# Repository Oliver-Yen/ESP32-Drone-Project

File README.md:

# ESP32-Drone-Project
This following project gets idea from a previous, broken DIY_drone_kit, and uses the ESP32-C6-Module as the MCU, while being controlled via WIFI or BT

TODO Add a distance, aclel., presu. , and an easy battery moniter    
TODO Add MOSFETs to drive the 4 coreless moters    
TODO Sch. drawing & PCB designing    
TODO Hardware code upload    
TODO HTML page design

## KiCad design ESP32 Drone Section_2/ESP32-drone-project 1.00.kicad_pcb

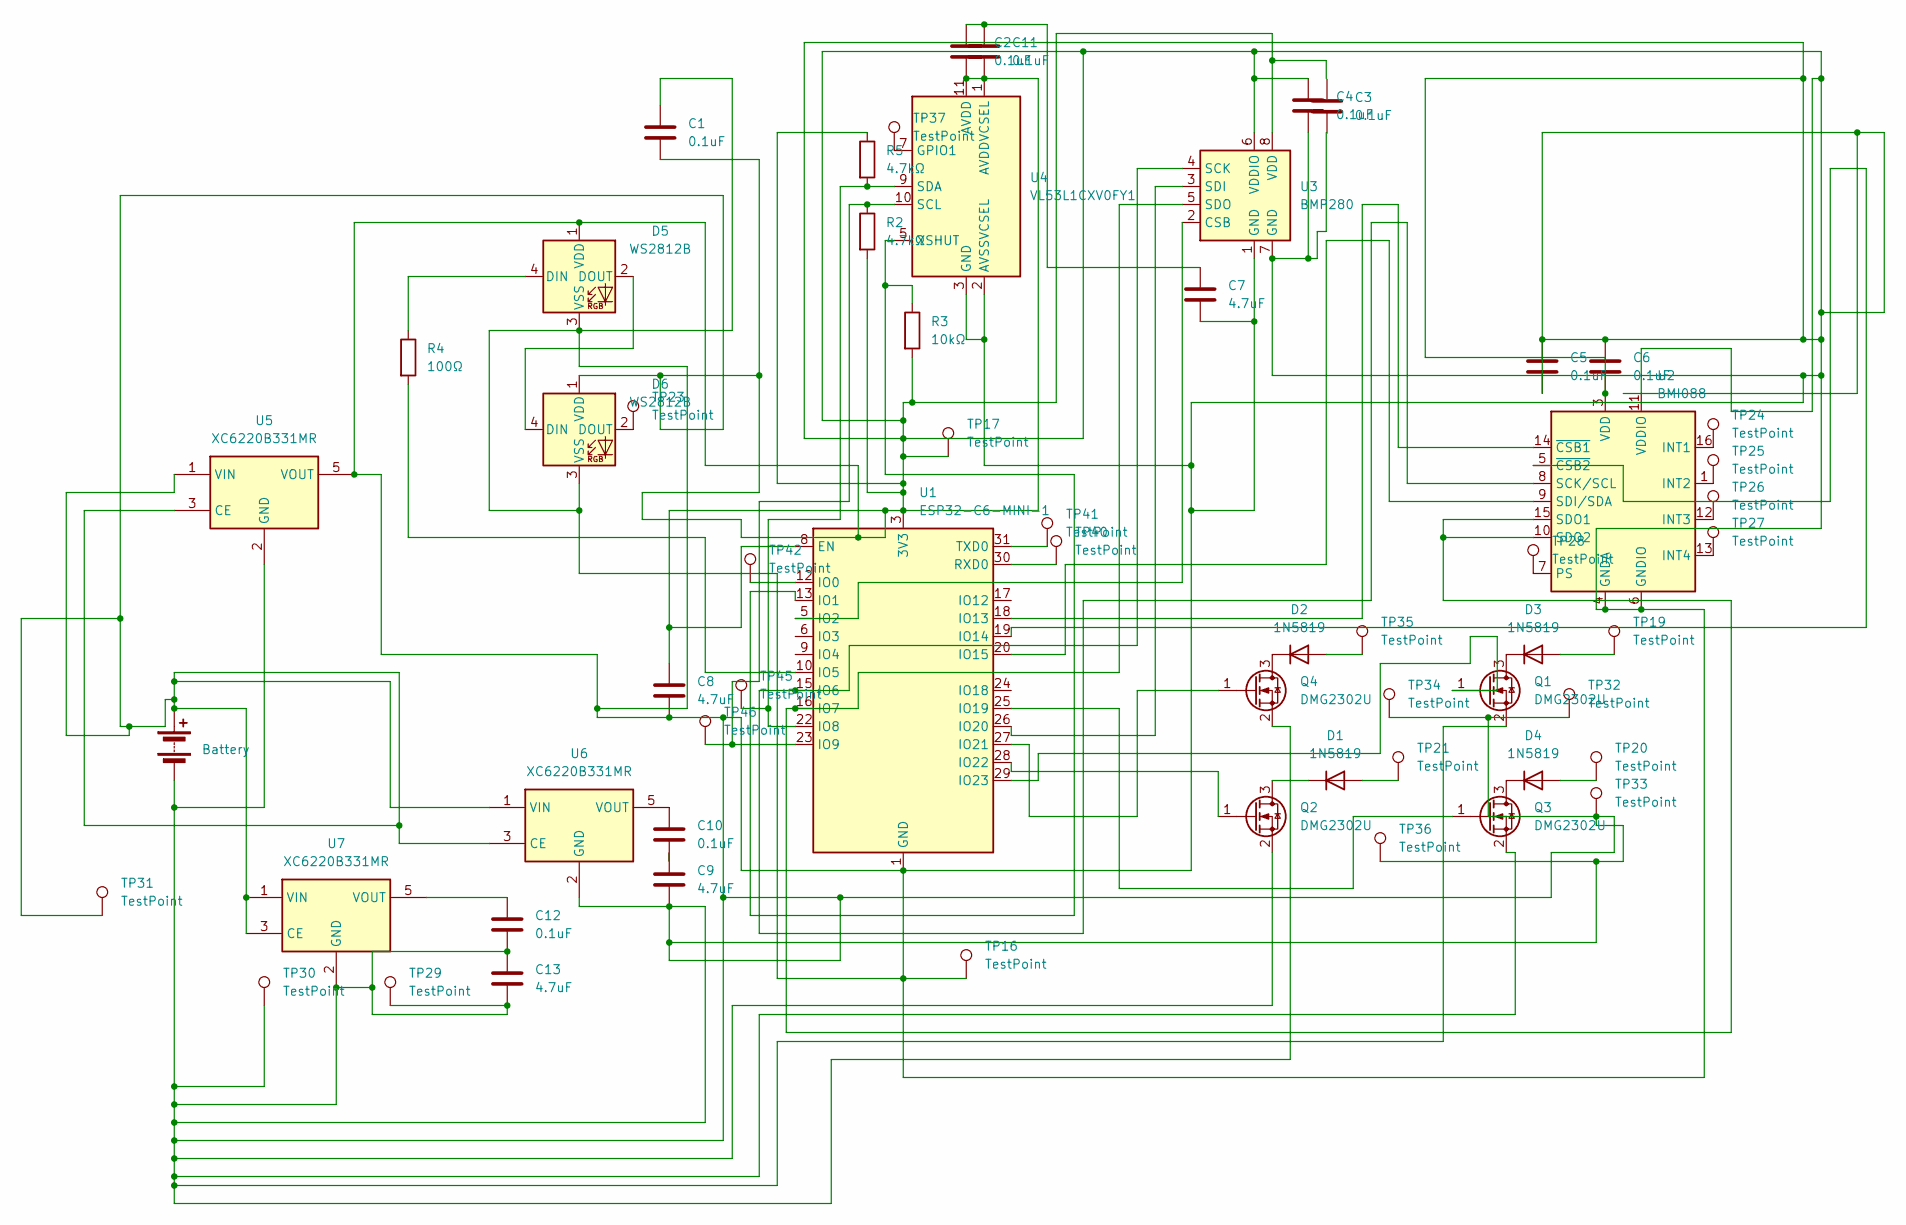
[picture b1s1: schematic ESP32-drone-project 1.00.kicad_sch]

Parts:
BT1: Battery
C1, C2, C3, C4, C5, C6, C11: 0.1uF; C_0603_1608Metric
C7: 4.7uF; C_0603_1608Metric
C8: 4.7uF
C9, C13: 4.7uF; C_0805_2012Metric
C10, C12: 0.1uF; C_0805_2012Metric
D1, D2, D3, D4: 1N5819; D_0805_2012Metric
D5, D6: WS2812B; LED_WS2812B_PLCC4_5.0x5.0mm_P3.2mm
Q1, Q2, Q3, Q4: DMG2302U; SOT-23
R2, R5: 4.7kΩ; R_0603_1608Metric
R3: 10kΩ; R_0603_1608Metric
R4: 100Ω; R_0603_1608Metric
TP16, TP17, TP29, TP30, TP31: TestPoint; TestPoint_Pad_1.5x1.5mm
TP19, TP20, TP21, TP32, TP33, TP34, TP35, TP36: TestPoint; PinHeader_1x01_P2.54mm_Horizontal
TP23, TP24, TP25, TP26, TP27, TP28, TP37, TP40, TP41, TP42, TP45, TP46: TestPoint; TestPoint_Pad_D1.0mm
U1: ESP32-C6-MINI-1
U2: BMI088; Bosch_LGA-16_4.5x3mm_P0.5mm_LayoutBorder7x1y_ClockwisePinNu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
U3: BMP280; Bosch_LGA-8_2x2.5mm_P0.65mm_ClockwisePinNumbering
U4: VL53L1CXV0FY1; ST_VL53L1x
U5, U6, U7: XC6220B331MR; SOT-23-5

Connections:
unnamed: BT1.1 (+), BT1.2 (-), C1.1, C1.2, C2.2, C4.1, C4.2, C5.1, C5.2, C6.1, C6.2, C7.2, C8.1, C8.2, C9.2, C11.2, C12.2, C13.1, C13.2, D5.1 (VDD), D5.3 (VSS), D6.1 (VDD), D6.3 (VSS), Q1.2 (S), Q2.2 (S), Q3.2 (S), Q4.2 (S), R2.2, R3.2, R5.1, TP16.1 (1_1), TP17.1 (1_1), TP29.1 (1_1), TP30.1 (1_1), TP31.1 (1_1), TP32.1 (1_1), TP33.1 (1_1), TP34.1 (1_1), TP36.1 (1_1), U1.1 (GND), U1.2 (GND), U1.3 (3V3), U1.8 (EN), U1.11 (GND), U1.14 (GND), U1.36 (GND), U1.37 (GND), U1.38 (GND), U1.39 (GND), U1.40 (GND), U1.41 (GND), U1.42 (GND), U1.43 (GND), U1.44 (GND), U1.45 (GND), U1.46 (GND), U1.47 (GND), U1.48 (GND), U1.49 (GND), U1.50 (GND), U1.51 (GND), U1.52 (GND), U1.53 (GND), U2.2 (GNDA), U2.3 (VDD), U2.4 (GNDA), U2.6 (GNDIO), U2.11 (VDDIO), U3.1 (GND), U3.6 (VDDIO), U3.7 (GND), U3.8 (VDD), U4.1 (AVDDVCSEL), U4.2 (AVSSVCSEL), U4.3 (GND), U4.4 (GND), U4.6 (GND), U4.11 (AVDD), U4.12 (GND), U5.1 (VIN), U5.2 (GND), U5.3 (CE), U5.5 (VOUT), U6.1 (VIN), U6.2 (GND), U6.3 (CE), U7.1 (VIN), U7.2 (GND), U7.3 (CE)
unnamed: C9.1, C10.2
unnamed: C2.1, C7.1, C11.1
unnamed: D1.2 (A), TP21.1 (1_1)
unnamed: D1.1 (K), Q2.3 (D)
unnamed: D2.2 (A), TP35.1 (1_1)
unnamed: D2.1 (K), Q4.3 (D)
unnamed: D3.2 (A), TP19.1 (1_1)
unnamed: D3.1 (K), Q1.3 (D)
unnamed: D4.2 (A), TP20.1 (1_1)
unnamed: D4.1 (K), Q3.3 (D)
unnamed: D5.4 (DIN), R4.1
unnamed: D5.2 (DOUT), D6.4 (DIN)
unnamed: D6.2 (DOUT), TP23.1 (1_1)
unnamed: Q1.1 (G), U1.29 (IO23)
unnamed: Q2.1 (G), U1.28 (IO22)
unnamed: Q3.1 (G), U1.25 (IO19)
unnamed: Q4.1 (G), U1.27 (IO21)
unnamed: TP42.1 (1_1), U1.12 (IO0)
unnamed: R3.1, U1.13 (IO1), U4.5 (XSHUT)
unnamed: U1.5 (IO2), U3.2 (CSB)
unnamed: R4.2, U1.10 (IO5)
unnamed: U1.15 (IO6), U2.8 (SCK/SCL), U3.4 (SCK)
unnamed: U1.16 (IO7), U2.10 (SDO2), U2.15 (SDO1), U3.5 (SDO)
unnamed: R5.2, TP45.1 (1_1), U1.22 (IO8), U4.9 (SDA)
unnamed: R2.1, TP46.1 (1_1), U1.23 (IO9), U4.10 (SCL)
unnamed: U1.18 (IO13), U2.14 (~CSB1)
unnamed: U1.19 (IO14), U2.5 (~CSB2)
unnamed: U1.20 (IO15), U2.9 (SDI/SDA)
unnamed: U1.26 (IO20), U3.3 (SDI)
unnamed: TP40.1 (1_1), U1.30 (RXD0)
unnamed: TP41.1 (1_1), U1.31 (TXD0)
unnamed: TP24.1 (1_1), U2.16 (INT1)
unnamed: TP25.1 (1_1), U2.1 (INT2)
unnamed: TP26.1 (1_1), U2.12 (INT3)
unnamed: TP27.1 (1_1), U2.13 (INT4)
unnamed: TP28.1 (1_1), U2.7 (PS)
unnamed: TP37.1 (1_1), U4.7 (GPIO1)
unnamed: C10.1, U6.5 (VOUT)
unnamed: C12.1, U7.5 (VOUT)

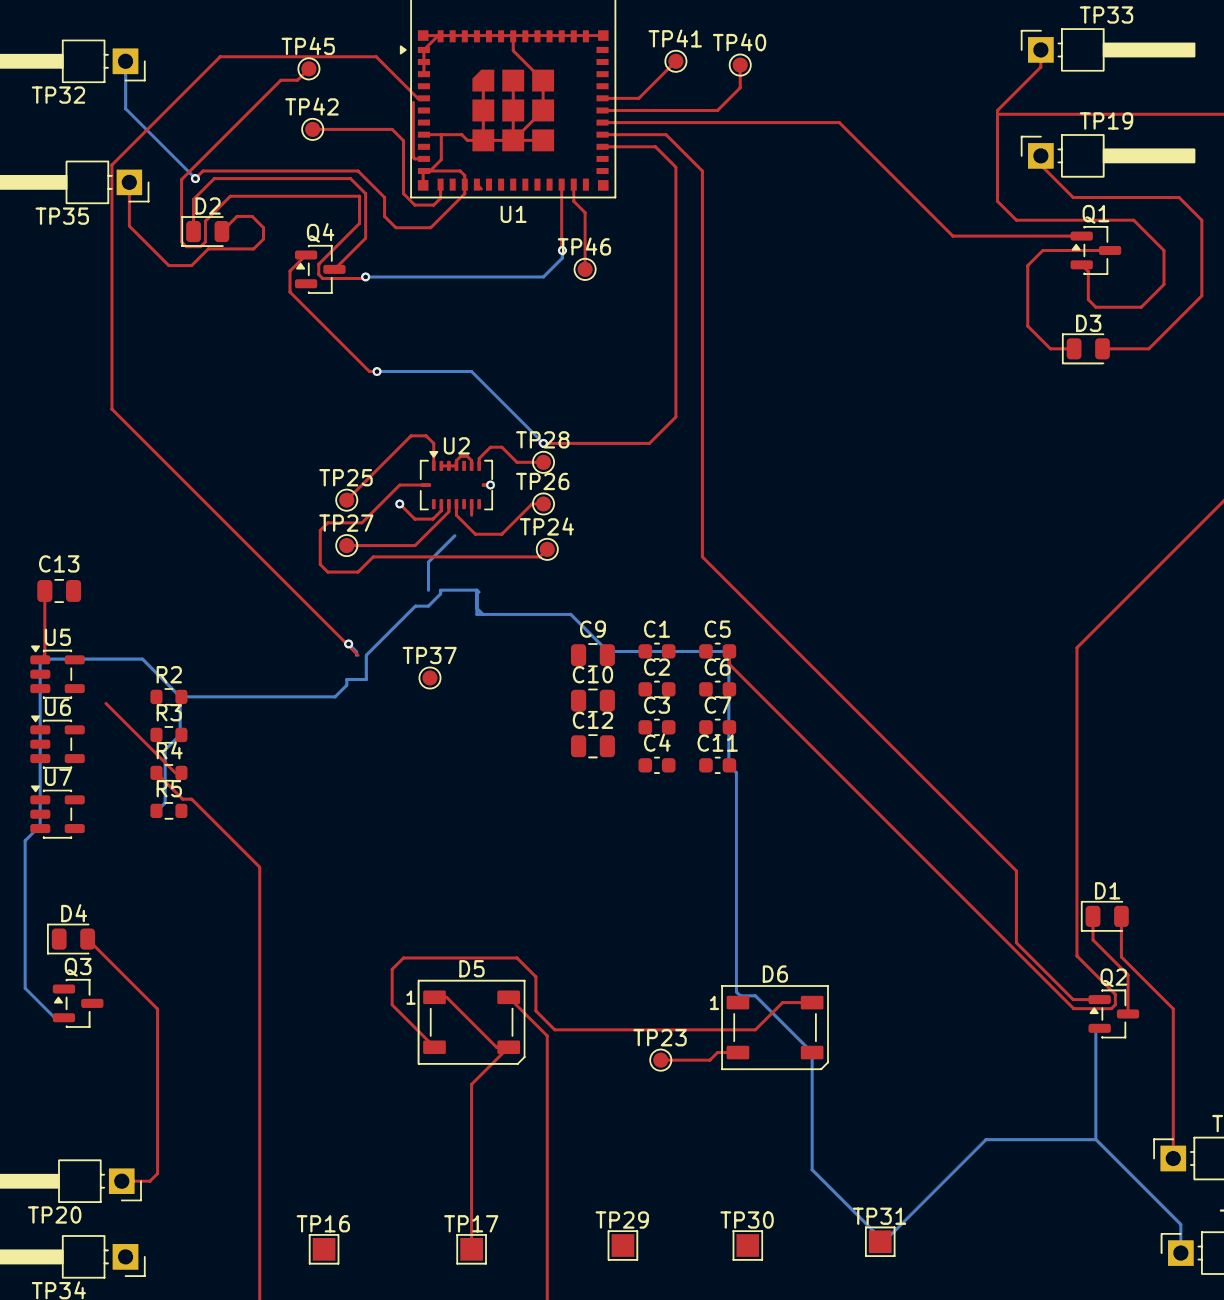
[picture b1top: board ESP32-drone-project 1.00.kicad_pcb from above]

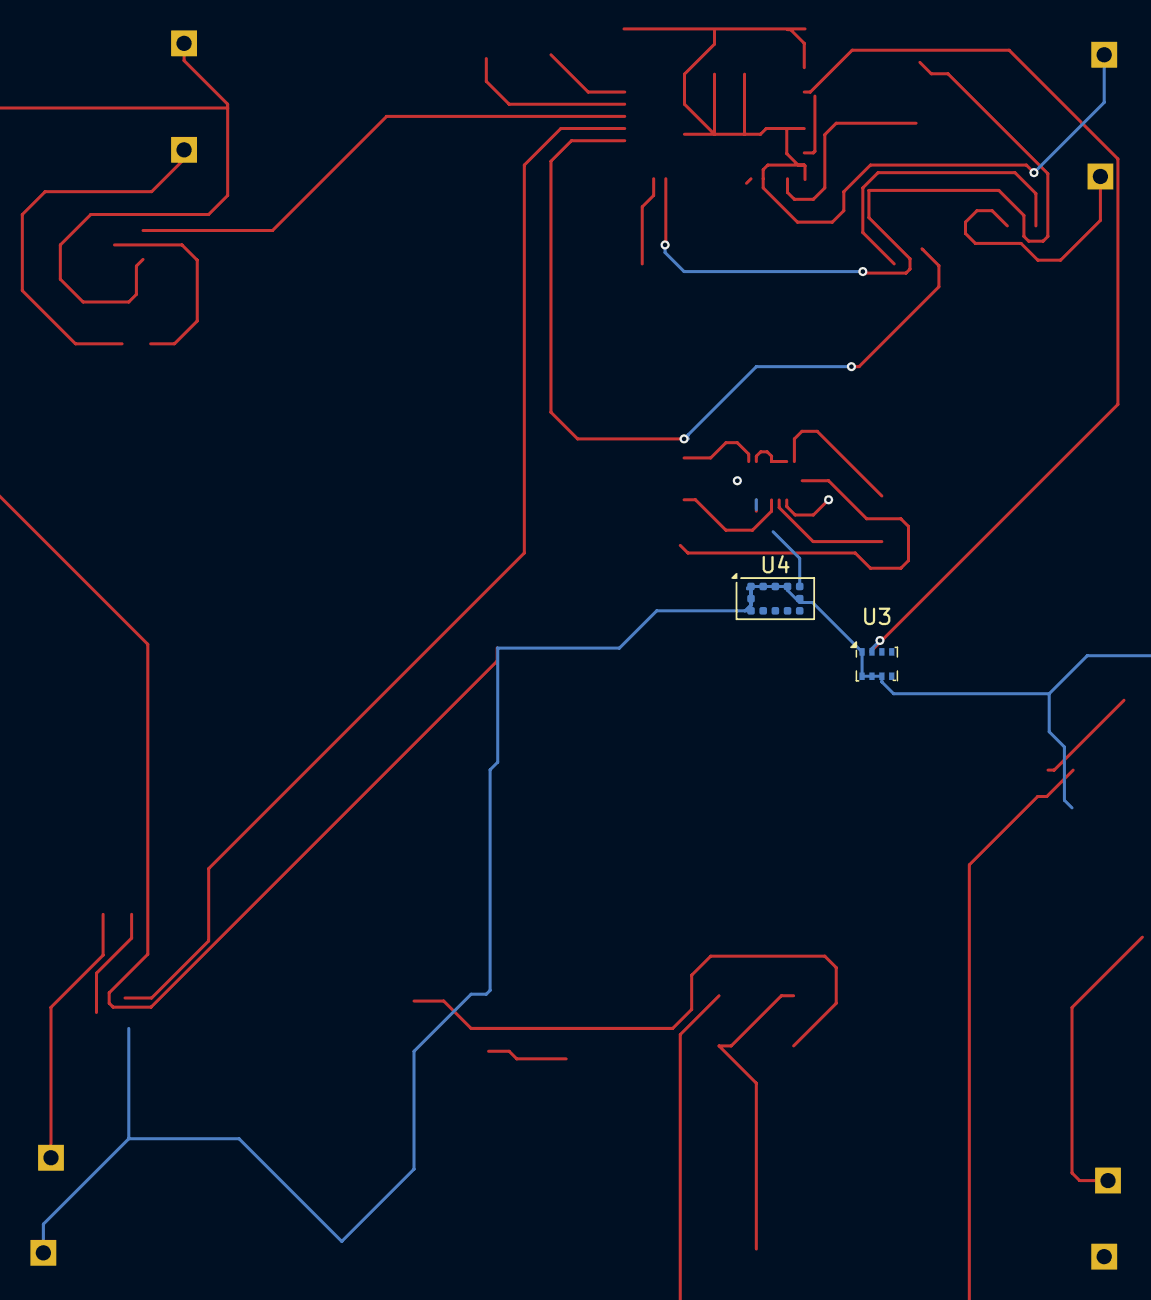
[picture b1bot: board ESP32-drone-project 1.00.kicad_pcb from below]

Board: 2 copper layers, 58 parts (2 on the bottom side), 40 nets.
